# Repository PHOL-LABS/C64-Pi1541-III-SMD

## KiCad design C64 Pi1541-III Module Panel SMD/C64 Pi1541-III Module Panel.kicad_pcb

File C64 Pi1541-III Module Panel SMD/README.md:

# Pi1541-III Module Panel
This PCB holds the components for the front panel, it was designed to mount on top of [Pi1541-III Module](https://github.com/tebl/C64-Pi1541-III/tree/main/C64%20Pi1541-III%20Module). This panel has its own BOM, so keep that in mind when ordering components - as you'll be needing parts listed for both of them to build a complete device.

- [1> Build instructions](#1-build-instructions)
- [2> Schematic](#2-schematic)
- [3> BOM](#3-bom)

# 1> Build instructions
Assembling this module is covered as part of the overall documentation, as linked below. Note that *BOM* is supplied per module, the one belonging to this module in particular is included as part of this document (click [here](#3-bom) to go there).
- [Assembling one](https://github.com/tebl/C64-Pi1541-III/blob/main/documentation/assembling_one.md)

# 2> Schematic
The supplied KiCad files should be sufficient as both a schematic and as a  starting point for ordering PCBs (basically you could just zip the contents of the export folder and upload that on a fabrication site), the schematic is also available in [PDF-format](https://github.com/tebl/C64-Pi1541-III/tree/main/documentation/schematic) and this is what you'll need to print and work your way through this things don't work as expected after assembly.

# 3> BOM
Most parts should be easy to get a hold of from your favourite local electronic component shop, but given that I don't have access to such shops where I live so everything was based on whatever I could get cheapest from eBay/AliExpress (free shipping, but plan on waiting 3-4 weeks for delivery). Components in parenthesis can be considered optional for features beyond the more basic functionality, but where's the fun in that? You deserve the complete package.

| Reference             | Item                                                              | Count | Order  |
| --------------------- | ----------------------------------------------------------------- | ----- | ------ |
| Module Panel PCB      | PCB specific to this project                                      |     1 | [See modules](https://github.com/tebl/C64-Pi1541-III/blob/main/README.md#1-modules)
| Faceplate (FP1) PCB   | Front faceplate                                                   |    (1)| [See modules](https://github.com/tebl/C64-Pi1541-III/blob/main/README.md#1-modules)
| IC1 *1                | SH1106 I2C OLED 128x64 (1.3")                                     |     1 |
| ENC1                  | EC11 rotary encoder, 20mm. Preferably plum handle.                |     1 |
|                       | Suitable knob for rotary encoder, max 20mm in diameter.           |    (1)|
| D1,D2                 | 2x5x7mm rectangular LED, suitably coloured.                       |     2 |
| J1                    | 12-pin right-angle pin header                                     |     1 |
| SW1,SW2               | 6x6mm momentary switch, 10.5mm or taller.                         |     2 |
| Mounting *2           | Nylon M3 hex standoffs 8mm (M-F)                                  |     4 |
| Mounting *2           | Nylon M3x6mm nylon screws                                         |     4 |
| Mounting *2           | Nylon M3x6mm nylon nuts                                           |     4 |

1) Many of these will be listed for sale as 1.3" ssd1306-based OLED displays, but they actually have the slightly different sh1106-controller. Something to keep in mind when ordering.
2) These are used in various places of the project, these are available in the form of kits usually advertised *M3 nylon standoff kit* which should contain most of what you'd need though you should check that they include them in sufficient quantity.

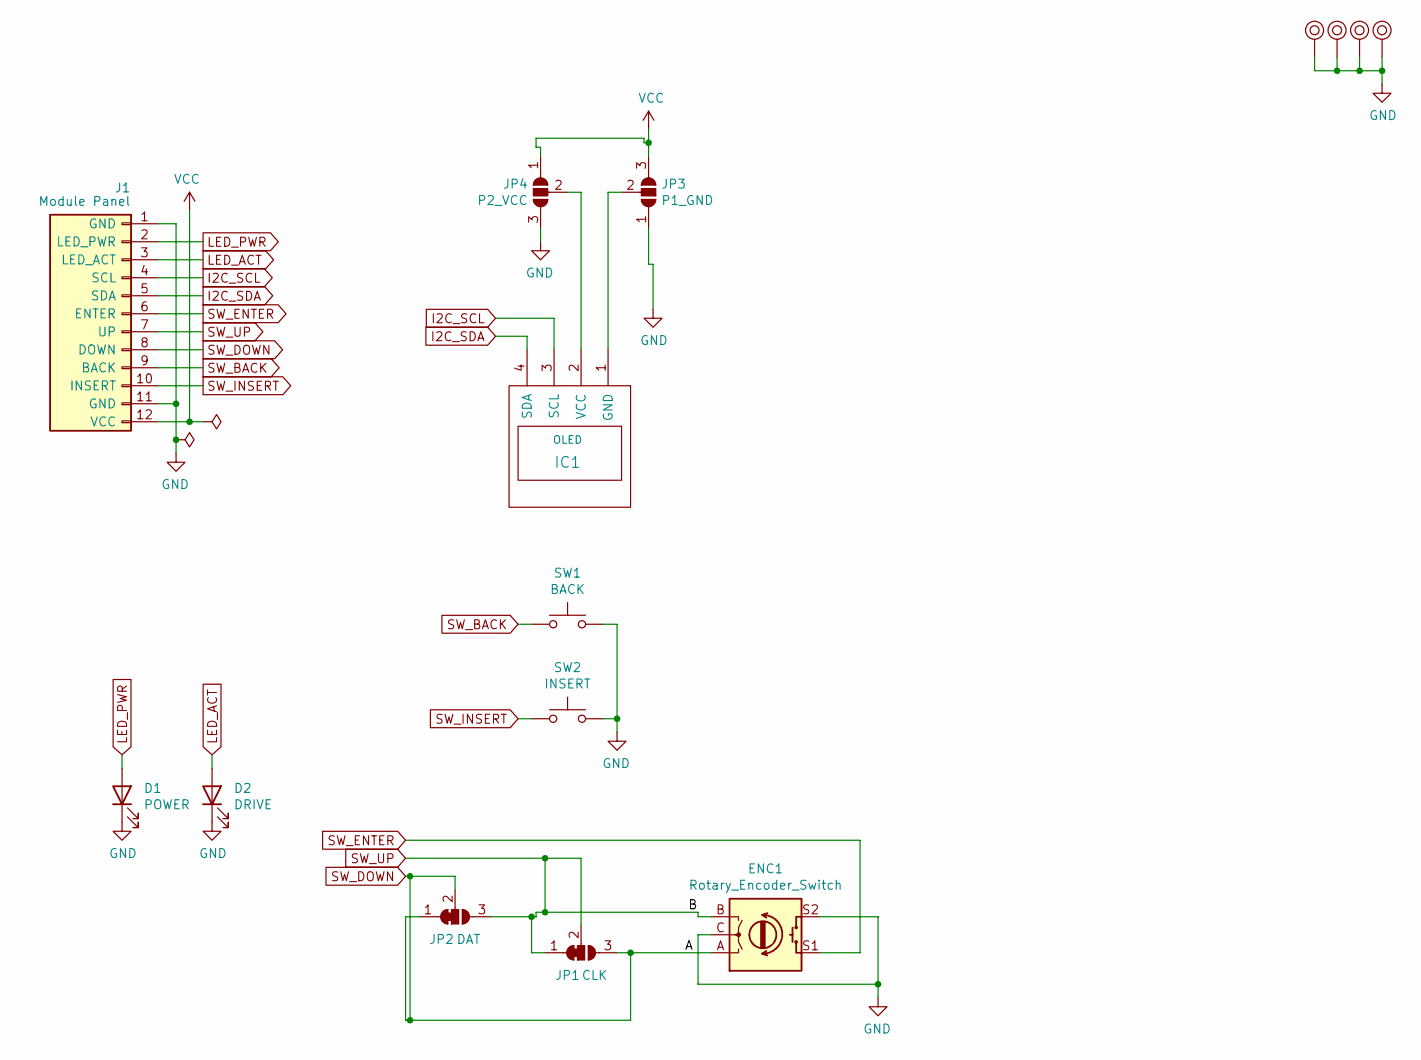
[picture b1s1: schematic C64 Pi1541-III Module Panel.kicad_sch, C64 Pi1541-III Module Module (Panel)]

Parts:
D1: POWER; LED_1206_3216Metric_Pad1.42x1.75mm_HandSolder
D2: DRIVE; LED_1206_3216Metric_Pad1.42x1.75mm_HandSolder
ENC1: Rotary_Encoder_Switch; RotaryEncoder_Alps_EC11E-Switch_Vertical_H20mm
IC1: OLED; 1.3_I2C_OLED_No_mounting
J1: Module Panel; PinHeader_1x12_P2.54mm_Horizontal
JP1: CLK; SolderJumper-3_P1.3mm_Open_Pad1.0x1.5mm
JP2: DAT; SolderJumper-3_P1.3mm_Open_Pad1.0x1.5mm
JP3: P1_GND; SolderJumper-3_P1.3mm_Open_Pad1.0x1.5mm
JP4: P2_VCC; SolderJumper-3_P1.3mm_Open_Pad1.0x1.5mm
M1, M2, M3, M4: Mounting_Pin; M3_pin
SW1: BACK; SW_SPST_PTS645
SW2: INSERT; SW_SPST_PTS645

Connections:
GND: D1.1 (K), D2.1 (K), ENC1.C, ENC1.S2, J1.1 (GND), J1.11 (GND), JP3.1 (A), JP4.3 (B), M1.1, M2.1, M3.1, M4.1, SW1.2, SW2.2
I2C_SCL: IC1.3 (SCL), J1.4 (SCL)
I2C_SDA: IC1.4 (SDA), J1.5 (SDA)
LED_ACT: D2.2 (A), J1.3 (LED_ACT)
LED_PWR: D1.2 (A), J1.2 (LED_PWR)
unnamed: IC1.1 (GND), JP3.2 (C)
unnamed: IC1.2 (VCC), JP4.2 (C)
SW_BACK: J1.9 (BACK), SW1.1
SW_DOWN: ENC1.A, J1.8 (DOWN), JP1.3 (B), JP2.1 (A), JP2.2 (C)
SW_ENTER: ENC1.S1, J1.6 (ENTER)
SW_INSERT: J1.10 (INSERT), SW2.1
SW_UP: ENC1.B, J1.7 (UP), JP1.1 (A), JP1.2 (C), JP2.3 (B)
VCC: J1.12 (VCC), JP3.3 (B), JP4.1 (A)

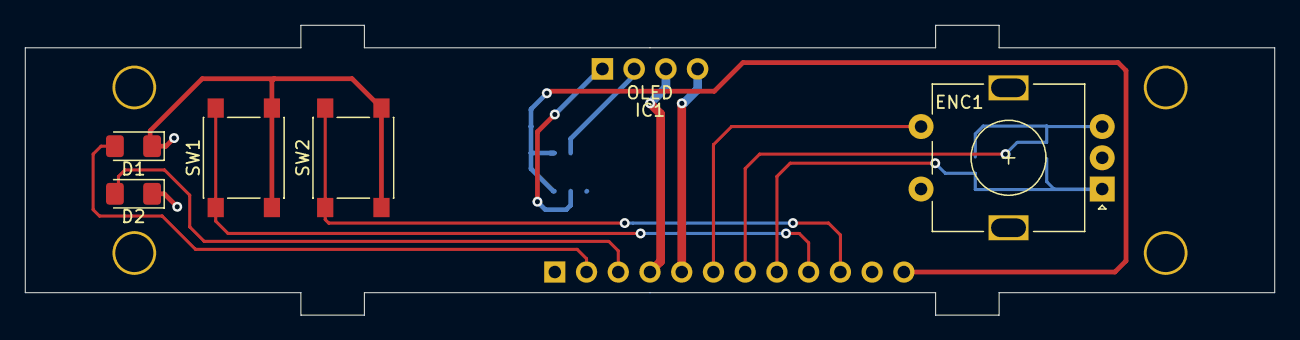
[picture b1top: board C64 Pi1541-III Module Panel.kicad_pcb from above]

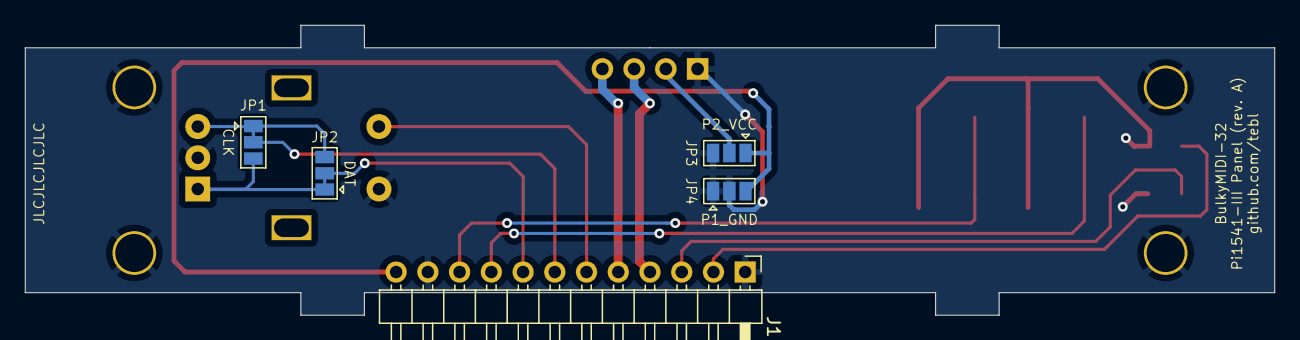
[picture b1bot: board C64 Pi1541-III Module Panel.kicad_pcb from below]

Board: 2 copper layers, 100.0 x 23.2 mm, 15 parts (5 on the bottom side), 13 nets.

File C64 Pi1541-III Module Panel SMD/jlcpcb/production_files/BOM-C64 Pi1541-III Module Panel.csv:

Comment,Designator,Footprint,LCSC,Quantity
Rotary_Encoder_Switch,ENC1,RotaryEncoder_Alps_EC11E-Switch_Vertical_H20mm,,1
INSERT,SW2,SW_SPST_PTS645,,1
BACK,SW1,SW_SPST_PTS645,,1
POWER,D1,LED_1206_3216Metric_Pad1.42x1.75mm_HandSolder,,1
DRIVE,D2,LED_1206_3216Metric_Pad1.42x1.75mm_HandSolder,,1
Module Panel,J1,PinHeader_1x12_P2.54mm_Horizontal,,1

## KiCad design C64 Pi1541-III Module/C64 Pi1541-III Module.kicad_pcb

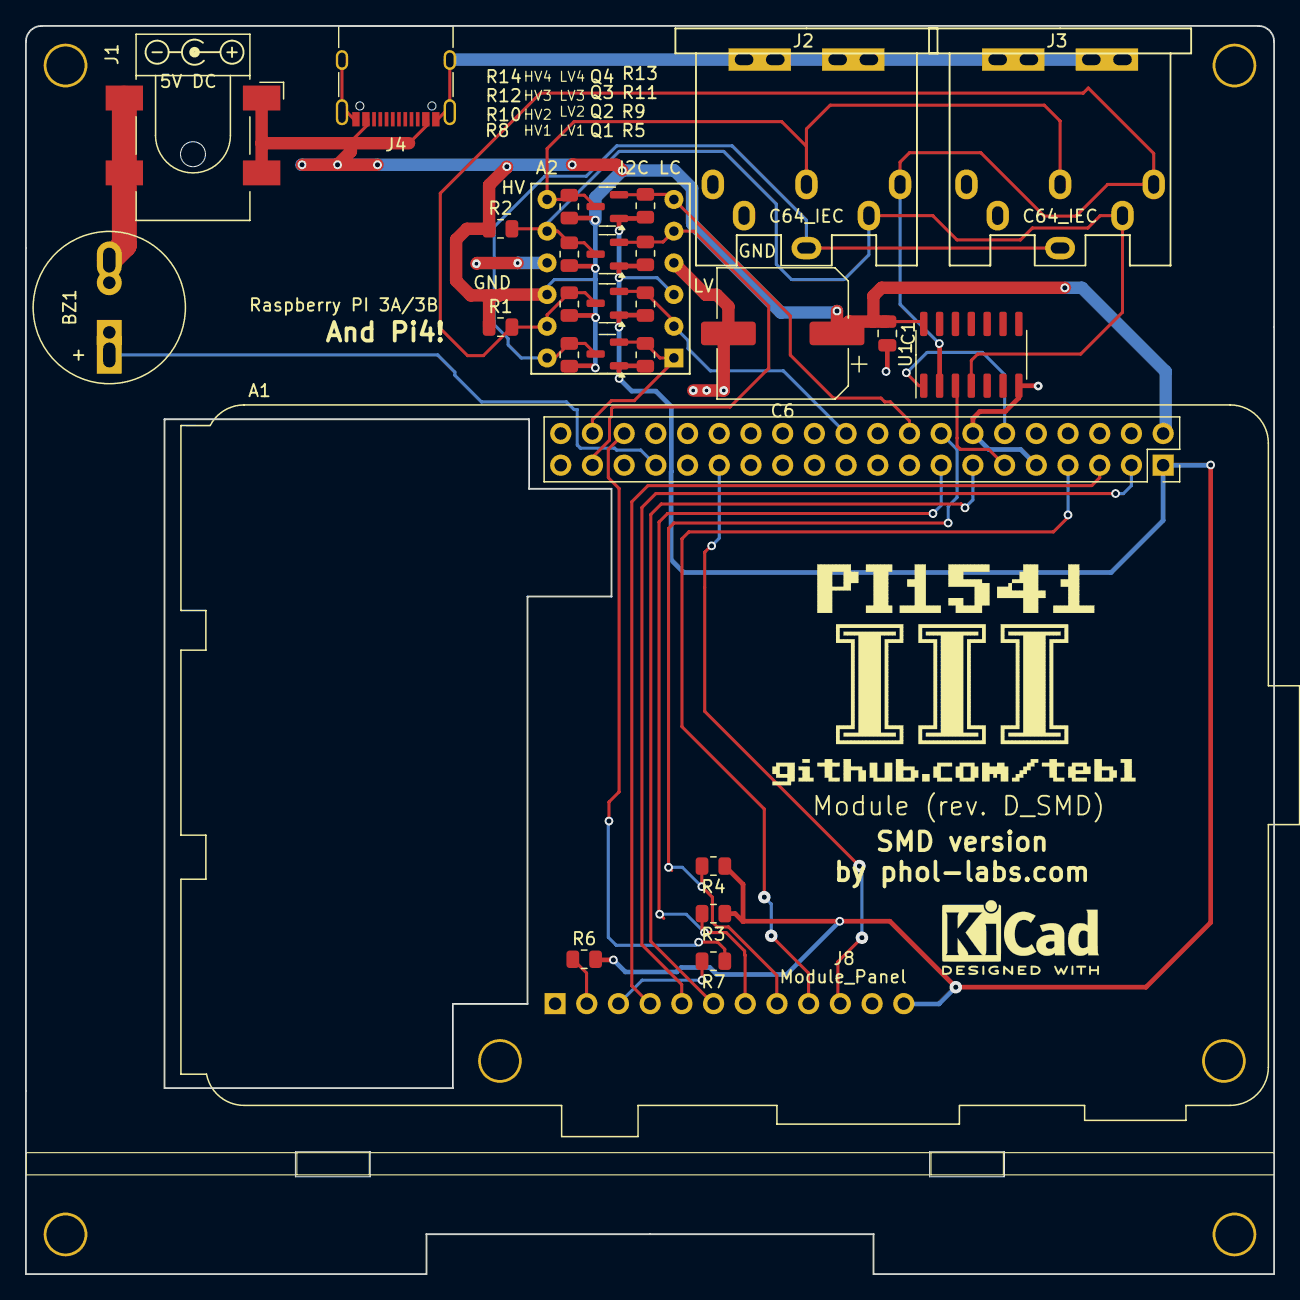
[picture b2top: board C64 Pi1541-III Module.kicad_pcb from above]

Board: 2 copper layers, 100.0 x 100.0 mm, 35 parts (1 on the bottom side), 24 nets.

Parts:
A1: Raspberry PI 3A/3B; Raspberry_Pi_3B_Socketed_THT_FaceDown_MountingHoles
A2: I2C LC; 4CH_I2C_Level_Converter
BZ1: Buzzer; Buzzer_12x9.5RM7.6
C1: 100nF; C_0805_2012Metric
C6: 470uF; CP_Elec_10x7.7
J1: DC IN; BarrelJack_CLIFF_FC681465S_SMT_Horizontal
J2, J3: C64_IEC; DIN6_IEC
J4: USB_C_Receptacle_USB2.0; USB_C_Receptacle_XKB_U262-16XN-4BVC11
J8: Module_Panel
M1, M2, M3, M4: Mounting; M3
Pi1541-drive: Pi1541-drive
Q1, Q2, Q3, Q4: DMG2302U; SOT-23
R1, R2: 1k; R_0805_2012Metric
R3, R4, R5, R8, R9, R10, R11, R12, R13, R14: 10k*; R_0805_2012Metric
R6, R7: 470*; R_0805_2012Metric
SYM1: DC_5V; PWR_Specification
U1: 7406; SO-14_3.9x8.65mm_P1.27mm

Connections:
+3V3: A1.1 (3V3), A2.3 (LV), J8.12 (VCC), Q1.1 (G), Q2.1 (G), Q3.1 (G), Q4.1 (G), R3.1, R4.1, R5.2, R6.2, R9.2, R11.2, R13.2
+5V: A1.2 (5V), A2.10 (HV), C1.1, C6.1, J1.1, J4.A4 (VBUS), J4.A9 (VBUS), J4.B4 (VBUS), J4.B9 (VBUS), R1.1, R2.1, R8.2, R10.2, R12.2, R14.2, U1.14 (VCC)
C64_ATN: A2.7 (HV4), J2.3, J3.3, Q4.3 (D), R14.1
C64_CLK: A2.8 (HV3), J2.4, J3.4, Q3.3 (D), R2.2, R12.1, U1.4 (2Y)
C64_DATA: A2.11 (HV2), J2.5, J3.5, Q2.3 (D), R1.2, R10.1, U1.2 (1Y)
C64_RST: A2.12 (HV1), J2.6, J3.6, Q1.3 (D), R8.1
GND: A1.6 (GND), A1.9 (GND), A1.14 (GND), A1.20 (GND), A1.25 (GND), A1.30 (GND), A1.34 (GND), A1.39 (GND), A2.4 (GND), A2.9 (GND), BZ1.2, C1.2, C6.2, J1.2, J1.3, J2.2, J2.7, J3.2, J3.7, J4.A1 (GND), J4.A12 (GND), J4.B1 (GND), J4.B12 (GND), J4.S1 (SHIELD), J8.1 (GND), J8.11 (GND), U1.7 (GND)
I2C_SCL: A1.5 (SCL/GPIO3), J8.4 (SCL)
I2C_SDA: A1.3 (SDA/GPIO2), J8.5 (SDA)
LED_ACT: J8.3 (LED_ACT), R7.2
LED_PWR: J8.2 (LED_PWR), R6.1
unnamed: A1.33 (PWM1/GPIO13), BZ1.1
RPI_ATN: A1.18 (GPIO24), A2.6 (LV4), Q4.2 (S), R13.1
RPI_CLK_IN: A1.37 (GPIO26), A2.5 (LV3), Q3.2 (S), R11.1
RPI_CLK_OUT: A1.11 (GPIO17), U1.3 (2A)
RPI_DATA_IN: A1.22 (GPIO25), A2.2 (LV2), Q2.2 (S), R9.1
RPI_DATA_OUT: A1.12 (GPIO18/PWM0), U1.1 (1A)
RPI_LED: A1.36 (GPIO16), R7.1
RPI_RST: A1.38 (GPIO20/MOSI1), A2.1 (LV1), Q1.2 (S), R5.1
SW1_ENTER: A1.13 (GPIO27), J8.6 (ENTER)
SW2_UP: A1.15 (GPIO22), J8.7 (UP), R3.2
SW3_DOWN: A1.16 (GPIO23), J8.8 (DOWN), R4.2
SW4_BACK: A1.7 (GCLK0/GPIO4), J8.9 (BACK)
SW5_INSERT: A1.29 (GCLK1/GPIO5), J8.10 (INSERT)

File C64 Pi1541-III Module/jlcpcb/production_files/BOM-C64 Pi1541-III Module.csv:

Comment,Designator,Footprint,LCSC,Quantity
DC IN,J1,BarrelJack_CLIFF_FC681465S_SMT_Horizontal,C114916,1
Raspberry PI 3A/3B,A1,Raspberry_Pi_3B_Socketed_THT_FaceDown_MountingHoles,C132132,1
USB_C_Receptacle_USB2.0,J4,USB_C_Receptacle_XKB_U262-16XN-4BVC11,C165948,1
10k*,"R10,R11,R12,R13,R14,R3,R4,R5,R8,R9",R_0805_2012Metric,C17414,10
1k,"R1,R2",R_0805_2012Metric,C17513,2
470*,"R6,R7",R_0805_2012Metric,C17710,2
Module_Panel,J8,Module_Panel,C247920,1
Buzzer,BZ1,Buzzer_12x9.5RM7.6,C252916,1
DMG2302U,"Q1,Q2,Q3,Q4",SOT-23,C427390,4
100nF,C1,C_0805_2012Metric,C49678,1
7406,U1,SO-14_3.9x8.65mm_P1.27mm,C5592,1
470uF,C6,CP_Elec_10x7.7,C88671,1
C64_IEC,J2,DIN6_IEC,,1
C64_IEC,J3,DIN6_IEC,,1
